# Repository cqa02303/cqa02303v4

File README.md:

# cqa02303v4
v4 keyboard config for vial

自作キーボードのファームウェア処理を解説するためのサンプルコードです

解説は https://engineering.nifty.co.jp/ でやるかもしれません

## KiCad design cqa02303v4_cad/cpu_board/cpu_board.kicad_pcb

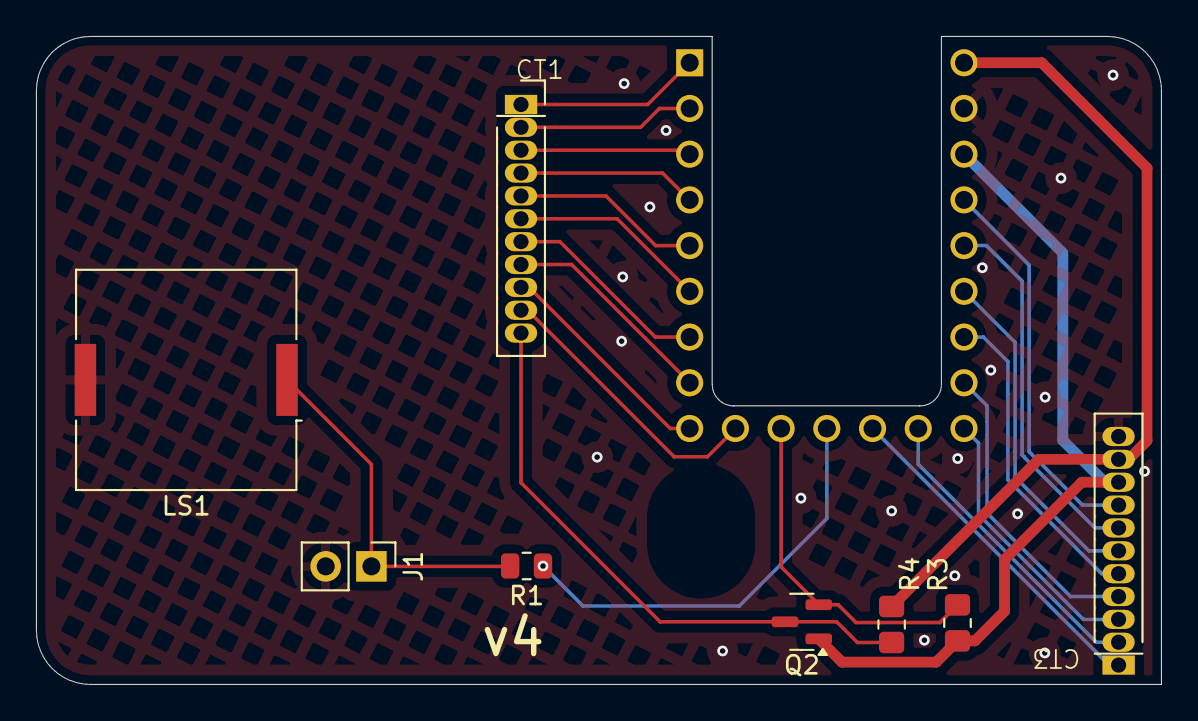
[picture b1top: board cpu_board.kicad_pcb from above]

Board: 2 copper layers, 62.5 x 36.0 mm, 10 parts (1 on the bottom side), 25 nets.

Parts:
CS_HL3: gh60_cpu_guard
CT1, CT3: ConnThrough_1x11_1.27mm
J1: Conn_01x02_Pin; PinHeader_1x02_P2.54mm_Vertical
LS1: Speaker; Buzzer_Murata_PKLCS1212E
Q2: BSS138; SOT-23
R1: 1k; R_0805_2012Metric
R3: 10K; R_0805_2012Metric_Pad1.20x1.40mm_HandSolder
R4: 560; R_0805_2012Metric_Pad1.20x1.40mm_HandSolder
U1: RP2040-ZERO; MODULE_RP2040-ZERO

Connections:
+3V3R: CT3.9, Q2.1 (G), R3.1, U1.21 (3V3)
+5VR: CT3.10, R4.1, U1.23 (5V)
GNDR: CT3.11, J1.2, LS1.2, U1.22 (GND)
unnamed: J1.1, LS1.1, R1.2
unnamed: CT1.11, Q2.3 (D), R4.2
unnamed: Q2.2 (S), R3.2, U1.11 (GP10)
unnamed: CT1.1, U1.1 (GP0)
unnamed: CT1.2, U1.2 (GP1)
unnamed: CT1.3, U1.3 (GP2)
unnamed: CT1.4, U1.4 (GP3)
unnamed: CT1.5, U1.5 (GP4)
unnamed: CT1.6, U1.6 (GP5)
unnamed: CT1.7, U1.7 (GP6)
unnamed: CT1.8, U1.8 (GP7)
unnamed: CT1.9, U1.9 (GP8)
unnamed: CT1.10, U1.10 (GP9)
unnamed: R1.1, U1.12 (GP11)
unnamed: CT3.1, U1.13 (GP12)
unnamed: CT3.2, U1.14 (GP13)
unnamed: CT3.3, U1.15 (GP14)
unnamed: CT3.4, U1.16 (GP15)
unnamed: CT3.5, U1.17 (GP26)
unnamed: CT3.6, U1.18 (GP27)
unnamed: CT3.7, U1.19 (GP28)
unnamed: CT3.8, U1.20 (GP29)

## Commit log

2025-05-08 KiCADv9.0データ追加
2025-05-09 ANALOG_JOYSTICK_AUTO_AXIS 対応
2025-05-14 レイヤー判定を訂正
